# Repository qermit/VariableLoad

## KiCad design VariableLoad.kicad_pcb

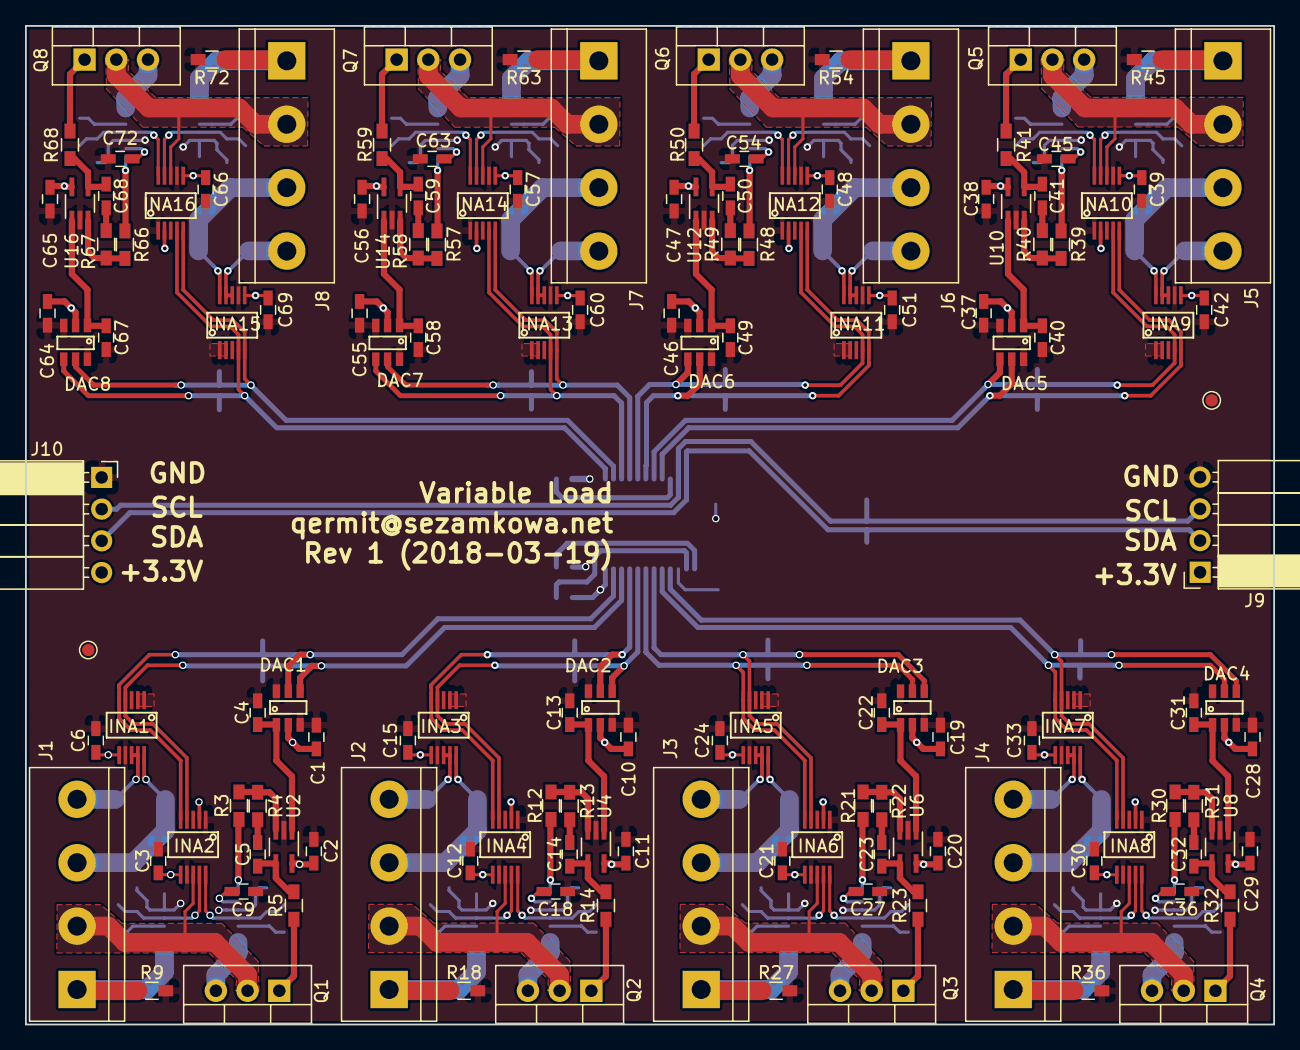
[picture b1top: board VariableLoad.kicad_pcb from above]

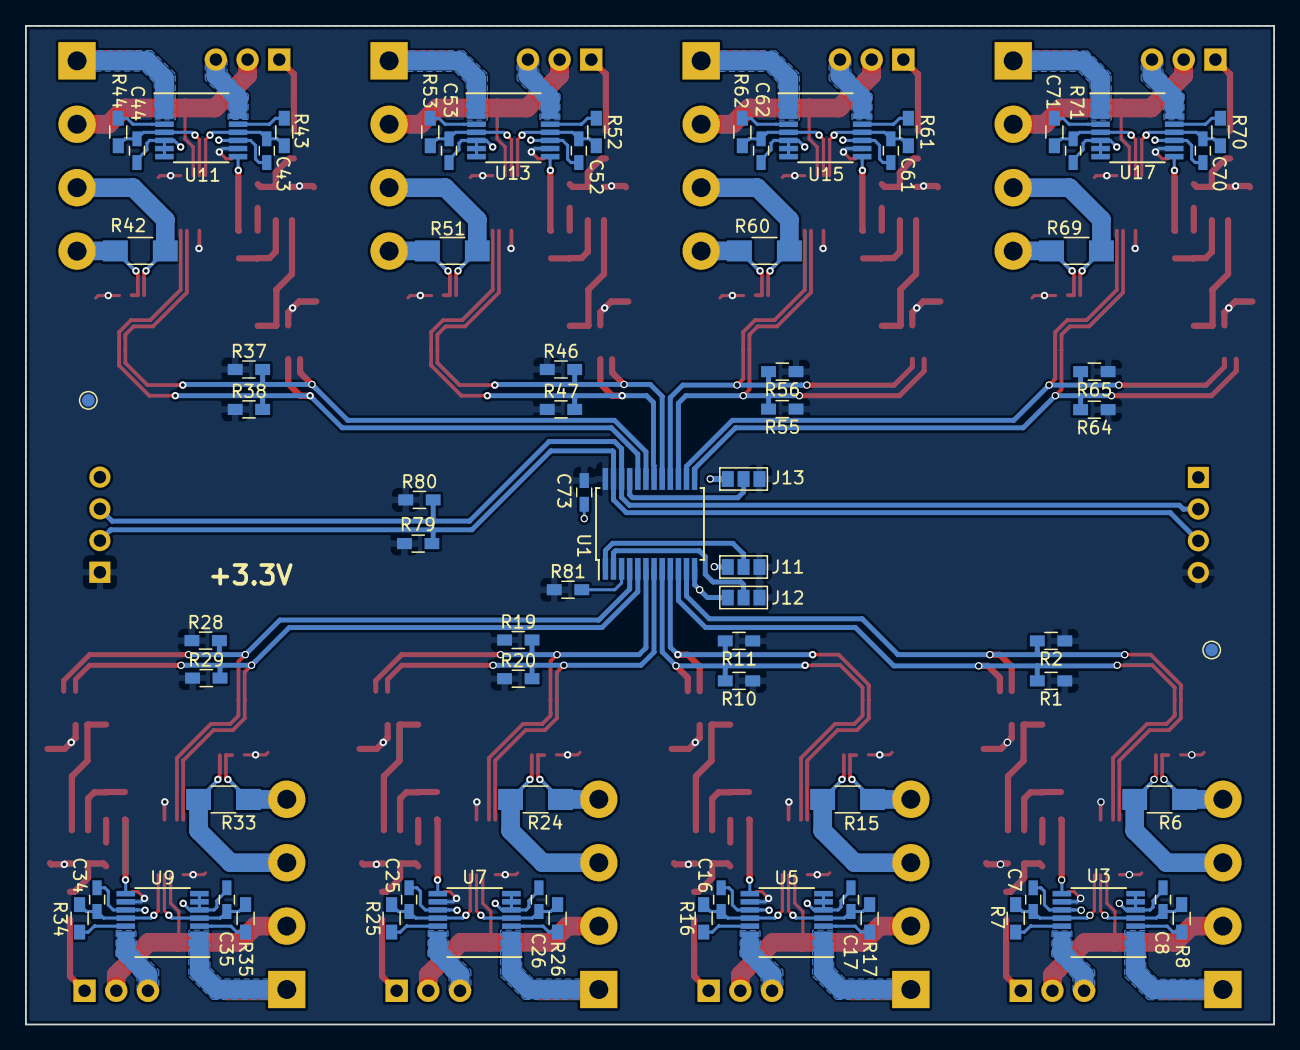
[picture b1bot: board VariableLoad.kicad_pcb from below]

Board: 2 copper layers, 100.0 x 80.0 mm, 214 parts (74 on the bottom side), 144 nets.

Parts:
C1, C2, C3, C4, C5, C6, C9, C10, C11, C12, C13, C14, C15, C18, C19, C20, C21, C22, C23, C24, C27, C28, C29, C30, C31, C32, C33, C36, C37, C38, C39, C40, C41, C42, C45, C46, C47, C48, C49, C50, C51, C54, C55, C56, C57, C58, C59, C60, C63, C64, C65, C66, C67, C68, C69, C72, C73: 100n; C_0603_HandSoldering
C7, C8, C16, C17, C25, C26, C34, C35, C43, C44, C52, C53, C61, C62, C70, C71: DNP; C_0603_HandSoldering
DAC1, DAC2, DAC3, DAC4, DAC5, DAC6, DAC7, DAC8: DAC081C081_(SOT); DAC081C081
INA1, INA2, INA3, INA4, INA5, INA6, INA7, INA8, INA9, INA10, INA11, INA12, INA13, INA14, INA15, INA16: INA220; ina220__smd_footprint
J1, J2, J3, J4, J5, J6, J7, J8: DNP; bornier4
J9: Conn_01x04_Male; Socket_Strip_Angled_1x04_Pitch2.54mm
J10: Conn_01x04_Female; Socket_Strip_Angled_1x04_Pitch2.54mm
J11, J12, J13: GS3
Q1, Q2, Q3, Q4, Q5, Q6, Q7, Q8: IRF540N; TO-220_Vertical
R1, R2, R3, R10, R11, R12, R19, R20, R21, R28, R29, R30, R37, R38, R39, R46, R47, R48, R55, R56, R57, R64, R65, R66, R79, R80, R81: 4k7; R_0603_HandSoldering
R4, R13, R22, R31, R40, R49, R58, R67: 100; R_0603_HandSoldering
R5, R14, R23, R32, R41, R50, R59, R68: 20; R_0603_HandSoldering
R6, R15, R24, R33, R42, R51, R60, R69: Riedon CSR1206-0R002F1; R_1206_HandSoldering
R7, R8, R9, R16, R17, R18, R25, R26, R27, R34, R35, R36, R43, R44, R45, R52, R53, R54, R61, R62, R63, R70, R71, R72: 0; R_0603_HandSoldering
TP1, TP2, TP3, TP4: TEST; TestPoint_Pad_D1.0mm
U1: PCA9548A; SSOP-24_5.3x8.2mm_Pitch0.65mm
U2, U4, U6, U8, U10, U12, U14, U16: LMV321; SOT-353_SC-70-5_Handsoldering
U3, U5, U7, U9, U11, U13, U15, U17: INA250A2PWR; TSSOP-16_4.4x5mm_Pitch0.65mm

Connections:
+3V3: C1.1, C2.1, C3.1, C6.2, C9.1, C10.1, C11.1, C12.1, C15.2, C18.1, C19.1, C20.1, C21.1, C24.2, C27.1, C28.1, C29.1, C30.1, C33.2, C36.1, C37.1, C38.1, C39.1, C42.2, C45.1, C46.1, C47.1, C48.1, C51.2, C54.1, C55.1, C56.1, C57.1, C60.2, C63.1, C64.1, C65.1, C66.1, C69.2, C72.1, C73.1, DAC1.2, DAC2.2, DAC3.2, DAC4.2, DAC5.2, DAC6.2, DAC7.2, DAC8.2, INA1.6, INA2.2, INA2.6, INA3.6, INA4.2, INA4.6, INA5.6, INA6.2, INA6.6, INA7.6, INA8.2, INA8.6, INA9.6, INA10.2, INA10.6, INA11.6, INA12.2, INA12.6, INA13.6, INA14.2, INA14.6, INA15.6, INA16.2, INA16.6, J9.1, J10.4, J11.1, J12.1, J13.1, R1.1, R2.1, R10.1, R11.1, R19.1, R20.1, R28.1, R29.1, R37.1, R38.1, R46.1, R47.1, R55.1, R56.1, R64.1, R65.1, R79.1, R80.1, R81.1, U1.24, U2.5, U3.10, U4.5, U5.10, U6.5, U7.10, U8.5, U9.10, U10.5, U11.10, U12.5, U13.10, U14.5, U15.10, U16.5, U17.10
/A0: J11.2, U1.1
/A1: J12.2, U1.2
/A2: J13.2, U1.21
/CurrentMonitor_1/Agnd: J4.1, R36.1, U9.1, U9.2, U9.3
/CurrentMonitor_1/Load: Q4.3, U9.14, U9.15, U9.16
/CurrentMonitor_1/V12in+: INA7.10, J4.3, R33.1
/CurrentMonitor_1/V12in-: INA7.8, INA7.9, J4.4, R33.2
/CurrentMonitor_1/Vbus: INA8.8, J4.2, Q4.2
/CurrentMonitor_1/Vin+: C34.1, INA8.10, R34.1, U9.12
/CurrentMonitor_1/Vin-: C35.2, INA8.9, R35.2, U9.5
/CurrentMonitor_1/Vset: C31.1, DAC4.1, U8.1
/CurrentMonitor_2/Agnd: J3.1, R27.1, U7.1, U7.2, U7.3
/CurrentMonitor_2/Load: Q3.3, U7.14, U7.15, U7.16
/CurrentMonitor_2/V12in+: INA5.10, J3.3, R24.1
/CurrentMonitor_2/V12in-: INA5.8, INA5.9, J3.4, R24.2
/CurrentMonitor_2/Vbus: INA6.8, J3.2, Q3.2
/CurrentMonitor_2/Vin+: C25.1, INA6.10, R25.1, U7.12
/CurrentMonitor_2/Vin-: C26.2, INA6.9, R26.2, U7.5
/CurrentMonitor_2/Vset: C22.1, DAC3.1, U6.1
/CurrentMonitor_3/Agnd: J2.1, R18.1, U5.1, U5.2, U5.3
/CurrentMonitor_3/Load: Q2.3, U5.14, U5.15, U5.16
/CurrentMonitor_3/V12in+: INA3.10, J2.3, R15.1
/CurrentMonitor_3/V12in-: INA3.8, INA3.9, J2.4, R15.2
/CurrentMonitor_3/Vbus: INA4.8, J2.2, Q2.2
/CurrentMonitor_3/Vin+: C16.1, INA4.10, R16.1, U5.12
/CurrentMonitor_3/Vin-: C17.2, INA4.9, R17.2, U5.5
/CurrentMonitor_3/Vset: C13.1, DAC2.1, U4.1
/CurrentMonitor_4/Agnd: J1.1, R9.1, U3.1, U3.2, U3.3
/CurrentMonitor_4/Load: Q1.3, U3.14, U3.15, U3.16
/CurrentMonitor_4/V12in+: INA1.10, J1.3, R6.1
/CurrentMonitor_4/V12in-: INA1.8, INA1.9, J1.4, R6.2
/CurrentMonitor_4/Vbus: INA2.8, J1.2, Q1.2
/CurrentMonitor_4/Vin+: C7.1, INA2.10, R7.1, U3.12
/CurrentMonitor_4/Vin-: C8.2, INA2.9, R8.2, U3.5
/CurrentMonitor_4/Vset: C4.1, DAC1.1, U2.1
/CurrentMonitor_5/Agnd: J5.1, R45.1, U11.1, U11.2, U11.3
/CurrentMonitor_5/Load: Q5.3, U11.14, U11.15, U11.16
/CurrentMonitor_5/V12in+: INA9.10, J5.3, R42.1
/CurrentMonitor_5/V12in-: INA9.8, INA9.9, J5.4, R42.2
/CurrentMonitor_5/Vbus: INA10.8, J5.2, Q5.2
/CurrentMonitor_5/Vin+: C43.1, INA10.10, R43.1, U11.12
/CurrentMonitor_5/Vin-: C44.2, INA10.9, R44.2, U11.5
/CurrentMonitor_5/Vset: C40.1, DAC5.1, U10.1
/CurrentMonitor_6/Agnd: J8.1, R72.1, U17.1, U17.2, U17.3
/CurrentMonitor_6/Load: Q8.3, U17.14, U17.15, U17.16
/CurrentMonitor_6/V12in+: INA15.10, J8.3, R69.1
/CurrentMonitor_6/V12in-: INA15.8, INA15.9, J8.4, R69.2
/CurrentMonitor_6/Vbus: INA16.8, J8.2, Q8.2
/CurrentMonitor_6/Vin+: C70.1, INA16.10, R70.1, U17.12
/CurrentMonitor_6/Vin-: C71.2, INA16.9, R71.2, U17.5
/CurrentMonitor_6/Vset: C67.1, DAC8.1, U16.1
/CurrentMonitor_7/Agnd: J7.1, R63.1, U15.1, U15.2, U15.3
/CurrentMonitor_7/Load: Q7.3, U15.14, U15.15, U15.16
/CurrentMonitor_7/V12in+: INA13.10, J7.3, R60.1
/CurrentMonitor_7/V12in-: INA13.8, INA13.9, J7.4, R60.2
/CurrentMonitor_7/Vbus: INA14.8, J7.2, Q7.2
/CurrentMonitor_7/Vin+: C61.1, INA14.10, R61.1, U15.12
/CurrentMonitor_7/Vin-: C62.2, INA14.9, R62.2, U15.5
/CurrentMonitor_7/Vset: C58.1, DAC7.1, U14.1
/CurrentMonitor_8/Agnd: J6.1, R54.1, U13.1, U13.2, U13.3
/CurrentMonitor_8/Load: Q6.3, U13.14, U13.15, U13.16
/CurrentMonitor_8/V12in+: INA11.10, J6.3, R51.1
/CurrentMonitor_8/V12in-: INA11.8, INA11.9, J6.4, R51.2
/CurrentMonitor_8/Vbus: INA12.8, J6.2, Q6.2
/CurrentMonitor_8/Vin+: C52.1, INA12.10, R52.1, U13.12
/CurrentMonitor_8/Vin-: C53.2, INA12.9, R53.2, U13.5
/CurrentMonitor_8/Vset: C49.1, DAC6.1, U12.1
/SCL: J9.3, J10.2, R80.2, U1.22
/SCL0: DAC4.5, INA7.5, INA8.5, R29.2, U1.5
/SCL1: DAC3.5, INA5.5, INA6.5, R20.2, U1.7
/SCL2: DAC2.5, INA3.5, INA4.5, R11.2, U1.9
/SCL3: DAC1.5, INA1.5, INA2.5, R2.2, U1.11
/SCL4: DAC8.5, INA15.5, INA16.5, R65.2, U1.14
/SCL5: DAC7.5, INA13.5, INA14.5, R56.2, U1.16
/SCL6: DAC6.5, INA11.5, INA12.5, R47.2, U1.18
/SCL7: DAC5.5, INA9.5, INA10.5, R38.2, U1.20
/SDA: J9.2, J10.3, R79.2, U1.23
/SDA0: DAC4.4, INA7.4, INA8.4, R28.2, U1.4
/SDA1: DAC3.4, INA5.4, INA6.4, R19.2, U1.6
/SDA2: DAC2.4, INA3.4, INA4.4, R10.2, U1.8
/SDA3: DAC1.4, INA1.4, INA2.4, R1.2, U1.10
/SDA4: DAC8.4, INA15.4, INA16.4, R64.2, U1.13
/SDA5: DAC7.4, INA13.4, INA14.4, R55.2, U1.15
/SDA6: DAC6.4, INA11.4, INA12.4, R46.2, U1.17
/SDA7: DAC5.4, INA9.4, INA10.4, R37.2, U1.19
GND: C1.2, C2.2, C3.2, C4.2, C6.1, C7.2, C8.1, C9.2, C10.2, C11.2, C12.2, C13.2, C15.1, C16.2, C17.1, C18.2, C19.2, C20.2, C21.2, C22.2, C24.1, C25.2, C26.1, C27.2, C28.2, C29.2, C30.2, C31.2, C33.1, C34.2, C35.1, C36.2, C37.2, C38.2, C39.2, C40.2, C42.1, C43.2, C44.1, C45.2, C46.2, C47.2, C48.2, C49.2, C51.1, C52.2, C53.1, C54.2, C55.2, C56.2, C57.2, C58.2, C60.1, C61.2, C62.1, C63.2, C64.2, C65.2, C66.2, C67.2, C69.1, C70.2, C71.1, C72.2, C73.2, DAC1.3, DAC1.6, DAC2.3, DAC2.6, DAC3.3, DAC3.6, DAC4.3, DAC4.6, DAC5.3, DAC5.6, DAC6.3, DAC6.6, DAC7.3, DAC7.6, DAC8.3, DAC8.6, INA1.1, INA1.2, INA1.7, INA2.1, INA2.7, INA3.1, INA3.2, INA3.7, INA4.1, INA4.7, INA5.1, INA5.2, INA5.7, INA6.1, INA6.7, INA7.1, INA7.2, INA7.7, INA8.1, INA8.7, INA9.1, INA9.2, INA9.7, INA10.1, INA10.7, INA11.1, INA11.2, INA11.7, INA12.1, INA12.7, INA13.1, INA13.2, INA13.7, INA14.1, INA14.7, INA15.1, INA15.2, INA15.7, INA16.1, INA16.7, J9.4, J10.1, J11.3, J12.3, J13.3, R9.2, R18.2, R27.2, R36.2, R45.2, R54.2, R63.2, R72.2, U1.12, U2.2, U3.6, U3.7, U3.8, U3.11, U4.2, U5.6, U5.7, U5.8, U5.11, U6.2, U7.6, U7.7, U7.8, U7.11, U8.2, U9.6, U9.7, U9.8, U9.11, U10.2, U11.6, U11.7, U11.8, U11.11, U12.2, U13.6, U13.7, U13.8, U13.11, U14.2, U15.6, U15.7, U15.8, U15.11, U16.2, U17.6, U17.7, U17.8, U17.11
unnamed: C5.1, R4.2
unnamed: C5.2, R5.2, U2.4
unnamed: C14.1, R13.2
unnamed: C14.2, R14.2, U4.4
unnamed: C23.1, R22.2
unnamed: C23.2, R23.2, U6.4
unnamed: C32.1, R31.2
unnamed: C32.2, R32.2, U8.4
unnamed: C41.1, R40.2
unnamed: C41.2, R41.2, U10.4
unnamed: C50.1, R49.2
unnamed: C50.2, R50.2, U12.4
unnamed: C59.1, R58.2
unnamed: C59.2, R59.2, U14.4
unnamed: C68.1, R67.2
unnamed: C68.2, R68.2, U16.4
unnamed: Q1.1, R5.1
unnamed: Q2.1, R14.1
unnamed: Q3.1, R23.1
unnamed: Q4.1, R32.1
unnamed: Q5.1, R41.1
unnamed: Q6.1, R50.1
unnamed: Q7.1, R59.1
unnamed: Q8.1, R68.1
unnamed: R3.1, R4.1, U2.3
unnamed: R3.2, U3.9
unnamed: R7.2, U3.13
unnamed: R8.1, U3.4
unnamed: R12.1, R13.1, U4.3
unnamed: R12.2, U5.9
unnamed: R16.2, U5.13
unnamed: R17.1, U5.4
unnamed: R21.1, R22.1, U6.3
unnamed: R21.2, U7.9
unnamed: R25.2, U7.13
unnamed: R26.1, U7.4
unnamed: R30.1, R31.1, U8.3
unnamed: R30.2, U9.9
unnamed: R34.2, U9.13
unnamed: R35.1, U9.4
unnamed: R39.1, R40.1, U10.3
unnamed: R39.2, U11.9
unnamed: R43.2, U11.13
unnamed: R44.1, U11.4
unnamed: R48.1, R49.1, U12.3
unnamed: R48.2, U13.9
unnamed: R52.2, U13.13
unnamed: R53.1, U13.4
unnamed: R57.1, R58.1, U14.3
unnamed: R57.2, U15.9
unnamed: R61.2, U15.13
unnamed: R62.1, U15.4
unnamed: R66.1, R67.1, U16.3
unnamed: R66.2, U17.9
unnamed: R70.2, U17.13
unnamed: R71.1, U17.4
unnamed: R81.2, U1.3

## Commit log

2018-08-13 initial
